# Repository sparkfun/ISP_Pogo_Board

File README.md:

ISP Pogo Adapter
================

_[ISP Pogo Adapter (KIT-23451)](https://www.sparkfun.com/products/23451)_

This is a simple adapter board that allows you to adapt pogo pins to an 6-pin ISP header. 

Repository Contents
-------------------
* **/Hardware** - All Eagle design files (.brd, .sch)

Documentation
--------------

* **[Assembly Video](https://youtu.be/aZCB-krwbAk?si=Pytt60uzcoHceXtl)** - Tutorial video showing how to assembly the ISP Pogo Adapter.
* **[PogoBeds: SparkFun Production and Testing](https://www.sparkfun.com/tutorials/138)** - How We Use Pogo Boards
* **[Pocket AVR Programmer Hookup Guide](https://learn.sparkfun.com/tutorials/pocket-avr-programmer-hookup-guide)** - Basic hookup guide for the Pocket AVR Programmer. 
* **[Installing an Arduino Bootloader](https://learn.sparkfun.com/tutorials/installing-an-arduino-bootloader)**  - Example of installing an Arduino bootloader on an Atmega328P-based microcontrollers (i.e. Arduino Uno and RedBoard Programmed with Arduino) through the Arduino IDE and command line using avrdude.

Product Versions
----------------
* [KIT-23451](https://www.sparkfun.com/products/23451) - v1.0, without the polarized jumper wire cable
* [KIT-11591](https://www.sparkfun.com/products/11591) - v1.0

Version History
---------------
* v1.0 - Initial Release

License Information
-------------------
The hardware is released under [Creative Commons Share-alike 3.0](http://creativecommons.org/licenses/by-sa/3.0/).

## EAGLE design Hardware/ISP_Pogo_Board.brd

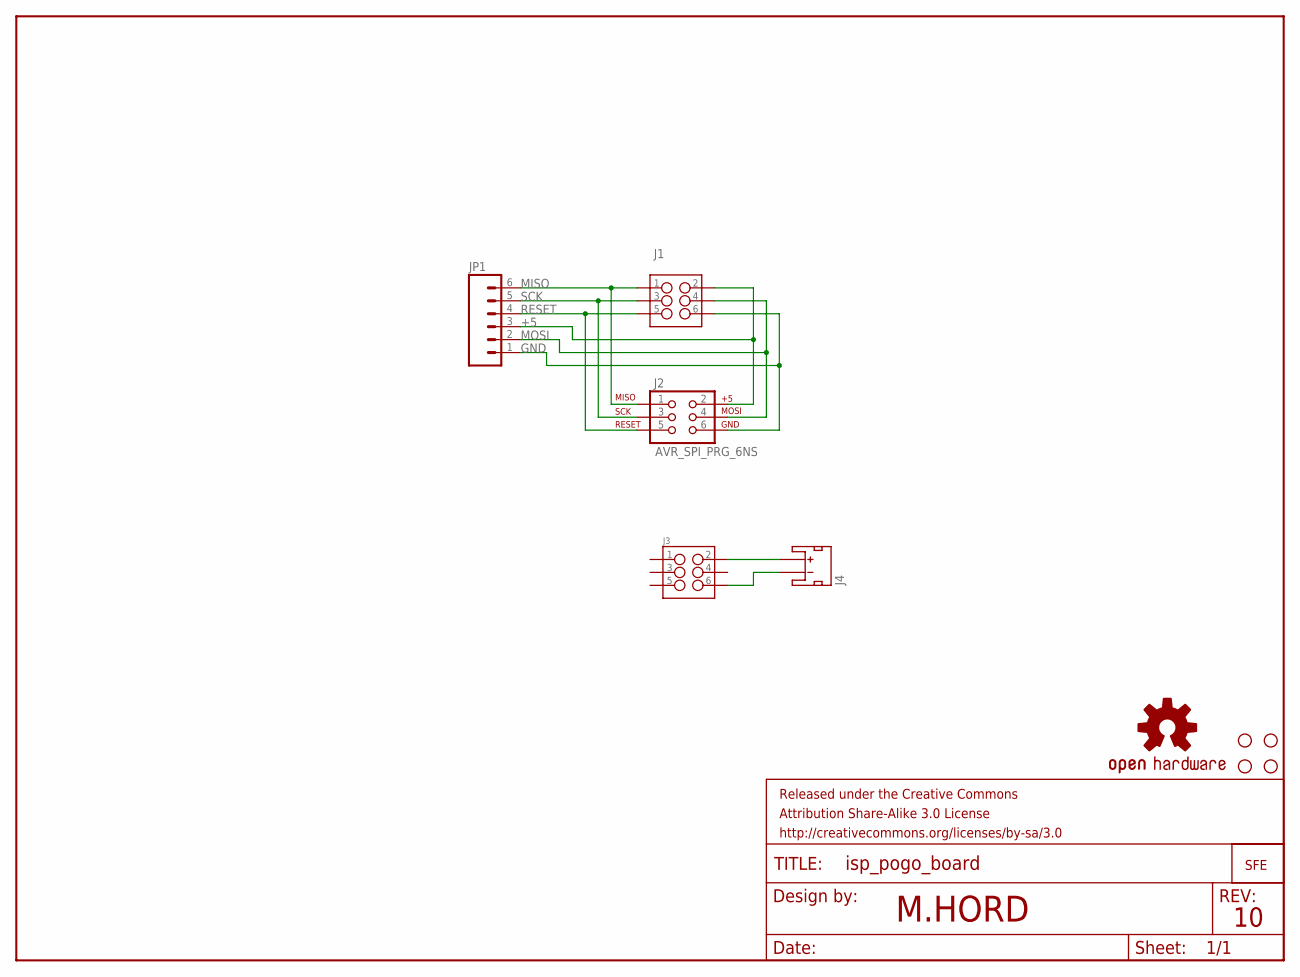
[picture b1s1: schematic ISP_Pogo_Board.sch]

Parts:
FRAME1: FRAME-LETTER; CREATIVE_COMMONS
J1, J3: M03X2POGO_PINS; 2X3_POGO
J2: AVR_SPI_PRG_6NS; 2X3-NS
J4: JST_2MM_MALE; JST-2-SMD
JP1: M06POLAR; MOLEX-1X6
JP2, JP3, JP4, JP5: STAND-OFF
JP6: LOGO-SFENW2; SFE-NEW-WEB
U$1: OSHW-LOGOS; OSHW-LOGO-S

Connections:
+5: J1.P$2 (2), J2.2, JP1.3
GND: J1.P$6 (6), J2.6, JP1.1
MISO: J1.P$1 (1), J2.1, JP1.6
MOSI: J1.P$4 (4), J2.4, JP1.2
unnamed: J3.P$2 (2), J4.2 (+)
unnamed: J3.P$6 (6), J4.1 (-)
RESET: J1.P$5 (5), J2.5, JP1.4
SCK: J1.P$3 (3), J2.3, JP1.5

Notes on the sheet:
M.HORD

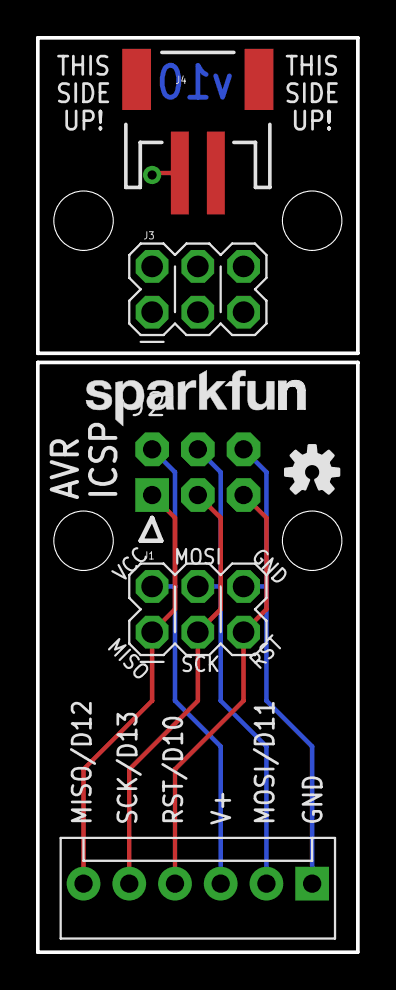
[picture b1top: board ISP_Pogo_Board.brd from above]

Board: 2 copper layers, 17.8 x 50.8 mm, 12 parts (0 on the bottom side), 8 nets.

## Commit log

2012-12-11 Initial commit- these are version 02 hardware files, which increase the size of the holes for the pogo pins (they were too tight on the initial proto run), adds "This Side Up" text to the bottom boar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
2012-12-18 Changed for v10: Made planes not overlap vscore region Increased annular ring on pogo pin pads
2013-08-19 Adding README

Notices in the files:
parts and their libraries:
SparkFun-Aesthetics: Licensing: CC v3.0 Share-Alike You are welcome to use this library for commercial purposes.
SparkFun-Aesthetics: Released under the Creative Commons Attribution Share-Alike 3.0 License
SparkFun-Aesthetics: Released under the Creative Commons
